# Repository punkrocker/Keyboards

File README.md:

# SweepPluck

34 键正交分体键盘，采用可翻面 PCB。两侧使用两片相同 PCB，在相反面装配。

本仓库仅包含 Pluck 版本。

- [工程、装配说明及验证结果](SweepPluck/README.txt)
- [主控焊接位置标记图](SweepPluck/mcu-guide/README.md)
- [电池与电源开关焊接图](SweepPluck/power-guide/README.md)
- [PCB 下单文件](SweepPluck/SweepPluck-JLCPCB.zip)
- [旅行便携盒](SweepPluck/travel-case/)
- [许可证](LICENSE)

设计基于 [Sweep](https://github.com/davidphilipbarr/Sweep)。Pluck 的历史设计归档保存在 `SweepPluck/archive/`。

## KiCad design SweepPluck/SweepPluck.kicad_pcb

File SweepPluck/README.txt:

SweepPluck v3.1 — 可翻面的正交分体键盘
======================================

电池与电源开关焊接图
  见 power-guide/README.md，含左手 F 面、右手 B 面焊盘图及焊接检查步骤。
  电池正极接 BATP1/BAT，负极接 BATG1/GND；开关 2–3 脚控制 BAT 到 RAW。

旅行便携盒
  travel-case/ 为裸 PCB + 3 mm 防滑垫配置的便携盒模型与 EVA 内托裁切图。
  轴体按 Choc V2，键帽高度按 K3 兼容矮键帽 4.4 mm 估算，主控为插座安装的 nice!nano。
  合拢外形约 108.05×92.80×44.80 mm；使用外部魔术贴绑带闭合。
  具体尺寸预算、安装限制和打印说明见 travel-case/使用说明.txt。
  tools/travel_case.py 可调整高度与主控安装间距预算；尚未实物试印。
  case/ 是之前的可选键盘底壳方案，使用上述旅行盒不需要制作该底壳。
  下方原有 ZIP 为此前生成的归档，不包含本次新增旅行盒，以目录中当前文件为准。

打开 SweepPluck.kicad_pro。
嘉立创 PCB 下单上传 SweepPluck-JLCPCB.zip。
它只包含 9 个生产层/钻孔文件，均位于 ZIP 根目录。
现在是一款 17 键单侧 PCB，同一份 Gerber 制作两片：
一片在 F 面安装键轴作为左手，另一片在 B 面安装键轴作为右手。
每片板都包含两种装配方式所需的孔和焊盘，不需要左右专用板。
原 v2 双侧拼板完整保存在 archive/SweepPluck-v2-panel.zip。

尺寸与布局
  整套 34 键，每侧 3×5 主键，加内侧第四排 2 个水平拇指键。
  键位与 v2 相同，全部为 0°，横纵键距均为 19.05 mm。
  单片 PCB 板框中心线尺寸：95.25×80.0 mm。
  板高由 77 mm 增至 80 mm，用于容纳主控的两组选装孔排。
  Gerber job 包围盒包含 0.05 mm 板框线宽，显示 95.30×80.05 mm。
  PCB 为 2 层 FR-4、1.6 mm 厚；USB/TRRS 插座可向板边外伸出。
  每片板有两个 3.2 mm 安装孔，仍位于原主键网格交点。
  此版本交付单片板；整套使用两片相同 PCB，没有折断桥。

主控焊接标记图
  见 mcu-guide/README.md，含左手 L 组、右手 R 组实际 PCB 标记及放大图。
  绿色圈出的两排共 24 孔为本侧主控焊孔，并标明 USB 朝向。

装配方法
  左手：将丝印 LEFT 的 F 面朝上，在此面装轴体、TRRS、电源及复位开关。
        主控装在 U1 的两排 L 孔中，USB 朝左侧外缘。
  右手：将丝印 RIGHT 的 B 面朝上，在此面装上述器件。
        主控装在同一 U1 封装的两排 R 孔中，USB 朝右侧外缘。

  主控区域共有四条横向孔排，按布局图方向从上到下依次为 L、R、L、R。
  左手选第 1 和第 3 排，右手选第 2 和第 4 排。
  两组选装孔排整体错开 2.54 mm，孔径为 1.0 mm。
  每组都是完整的 2×12 针 Pro Micro 接口，每块 PCB 只装一个主控。
  不需要 MCU 焊锡跳线，也不要短接另一组选装孔排。

  主控沿用 Sweep High M 的 FACE DOWN 安装方向：
  元件面、USB 插座所在面朝向键盘 PCB，而不是朝向键帽上方。
  用排针或插座留出元件和 USB 外壳的高度，不要将主控模块贴板焊接。
  两面均标有 FACE DOWN、L/R、TX 和 RAW，可用模块引脚标记核对方向。
  左手 L 组 USB 端的上排是 TX、下排是 RAW；
  右手 R 组从 B 面看 USB 端的上排是 RAW、下排是 TX。
  电源和复位开关均提供 F/B 两面焊盘，每个位置只在键轴所在面安装一个。
  轴体焊孔、TRRS 成对焊盘和电池通孔支持正反面装配。

轴体与电路
  保留原 Choc V1 / Choc V2 / MX / Alps 通用焊接兼容性，无热插拔。
  新轴体封装保留原钻孔中心并增加镜像孔位。
  MX/Alps 的两个无极性触点翻面后交换 GPIO/GND 接法；
  Choc 的中心触点仍接 GND，左右对称的另一触点接同一 GPIO。
  重叠的轴体圆孔/长孔已合并为连续镀铜长孔。
  中心定位孔为 4.9 mm，两侧定位孔仍为 2.17×1.8 mm NPTH 长孔。
  每侧 17 键直连，无矩阵二极管。
  两组选装孔的 24 针 GPIO、电源和复位映射均与 v2 左侧一致。
  每侧 68 个有效器件引脚连接与原设计核对一致。
  TRRS：R1=SERIAL（Pro Micro RX），R2=VCC，T/S=GND。
  电池正极 BAT 经电源开关接 RAW，负极接 GND，沿用原供电接法。
  引脚 CSV 包含网络、坐标、钻孔和 LEFT/RIGHT/BOTH 装配标记。
  预览数字 1–17 是 Switch1–Switch17 网络编号，不是实际键码。
  本次没有新增或烧录固件；左右手选择由对应 QMK/ZMK 固件配置。

定位板
  SweepPluck-plate.kicad_pcb / .dxf 是可翻面的单侧定位板，DXF 单位为毫米。
  两侧各用一片相同定位板，右手翻面使用。
  下方外侧开口避让两组选装主控及其他器件。
  默认 14×14 mm 轴孔供适配该尺寸的 MX/Choc 使用。
  Alps 定位板开口不同，使用 Alps 时需按实际轴体另改定位板。
  网格交点上的固定件需低于键帽活动空间，可使用平头/沉头方案。

交付文件
  SweepPluck-v3-reversible.zip：完整 v3 工程包，包含本地库、脚本、检查报告和来源归档。
  SweepPluck.kicad_pro / .kicad_pcb / .kicad_sch：v3 主工程。
  SweepPluck.kicad_sym、SweepPluck.pretty、库表：本地符号与可翻面封装。
  SweepPluck-preview.png / SweepPluck-layout.svg：左右手装配示意。
  SweepPluck-preview.svg / SweepPluck-preview-pcb.png：实际 F 面 PCB。
  SweepPluck-back.svg / SweepPluck-back-pcb.png：镜像显示的实际 B 面 PCB。
  SweepPluck-plate.kicad_pcb / .dxf / .svg：单侧定位板。
  SweepPluck-pins.csv：引脚、网络和孔排核对表。
  SweepPluck-JLCPCB.zip / SweepPluck-gerbers.zip：相同的专用下单包，共 9 文件。
    包含两面铜层、阻焊、丝印、GKO 板框和独立 PTH/NPTH 钻孔。
    使用标准 RS-274X、Protel 扩展名、毫米十进制 Excellon，绘图坐标为非负值。
    不含工程、嵌套压缩包、Gerber job 或 X2/网络扩展属性。
  gerbers/：KiCad 原始导出文件，另外保留一个 Gerber job，目录共 10 文件。
  verification/summary.json：最终检查结果与板文件、生产文件 SHA-256。
  verification/fabrication-check.json：对实际下单 ZIP 的独立 Gerbv 解析及开窗/钻孔核对报告。
  archive/SweepPluck-v2-panel.zip：改动前双侧拼板及全部配套文件。
  archive/SweepPluck-v1-split.zip：更早的左右独立工程。

验证与限制
  KiCad 10.0.7：PCB DRC 0 违规、0 未连接、0 原理图一致性问题。
  原理图 ERC 0 违规，定位板 DRC 0 违规。
  102 项触点检查覆盖每个键的 MX、Alps、Choc 两面安装接法。
  原 153 个轴体钻孔中心全部保留，原键位与 GPIO 映射核对通过。
  主控外形与键帽、定位板避让区核对通过。
  v3.1 修复了布线导入后通孔焊盘阻焊开窗丢失的问题。
  211 个通孔焊盘均有双面开窗；每面导出的 277 个开窗逐项核对通过。
  专用包 9 文件经 Gerbv 2.10.0 独立解析：0 错误、0 警告。
  镀铜钻孔/槽 222 个（包含过孔），非镀铜孔/槽 57 个，与 PCB 数量一致。
  尚未在嘉立创账户中完成在线上传实测。
  线宽 >=0.20 mm、电气间距 >=0.20 mm、铜到板边/钻孔 >=0.25 mm。
  走线为 0.25 mm，过孔为 0.60/0.30 mm。
  原理图为被动引脚连接图，ERC 不检查 MCU 引脚方向或模块供电/充电能力。
  尚未实物打样；插座高度、实际模块外形及轴体/定位板装配仍需打样确认。

重新生成（当前文件已生成，无需运行）
  使用能 import pcbnew 的 KiCad Python，并确保 kicad-cli 位于 PATH。
  cairosvg 用于 PNG 预览，布线需 Java 21 和 Freerouting 2.1.0。
  从仓库根目录运行：
    python SweepPluck/tools/reversible.py build
    python SweepPluck/tools/reversible.py route --jar /path/to/freerouting-2.1.0.jar
    python SweepPluck/tools/reversible.py import
    python SweepPluck/tools/reversible.py checks
  build 从 v2 归档重建 v3，会覆盖 PCB 为未布线版。
  若 checks 仅有 track_dangling 警告且无未连接项，运行：
    python SweepPluck/tools/reversible.py clean
  clean 只移除 DRC 明确报告的冗余支线，不忽略检查项。
  完成后：
    python SweepPluck/tools/reversible.py placement
    python SweepPluck/tools/reversible.py export
    python SweepPluck/tools/check_fabrication.py
  export 会先核对检查报告与当前 PCB、原理图、定位板及规则，再导出生产文件。
  check_fabrication 需安装 gerbv，检查专用下单包的实际文件与 PCB 数据。
  手动编辑 PCB 后可用 refresh 更新辅助文件，再执行 checks 和 export。
  compact.py 转发到同一 v3 生成器；preview.py 生成 v3 装配图。
  如需重新打包完整工程，运行 python SweepPluck/tools/package.py。

参考与授权
  原接口/键位来源为本仓库 Sweep High；可翻面结构参考 Sweep High M / Sweep Half Swept。
  主控安装方向参考 gallery/sweep-high-m/front.png 的 Face down 标记。
  nice!nano 引脚图：https://nicekeyboards.com/docs/nice-nano/pinout-schematic/
  Freerouting：https://github.com/freerouting/freerouting/releases/tag/v2.1.0
  授权沿用本仓库 LICENSE。

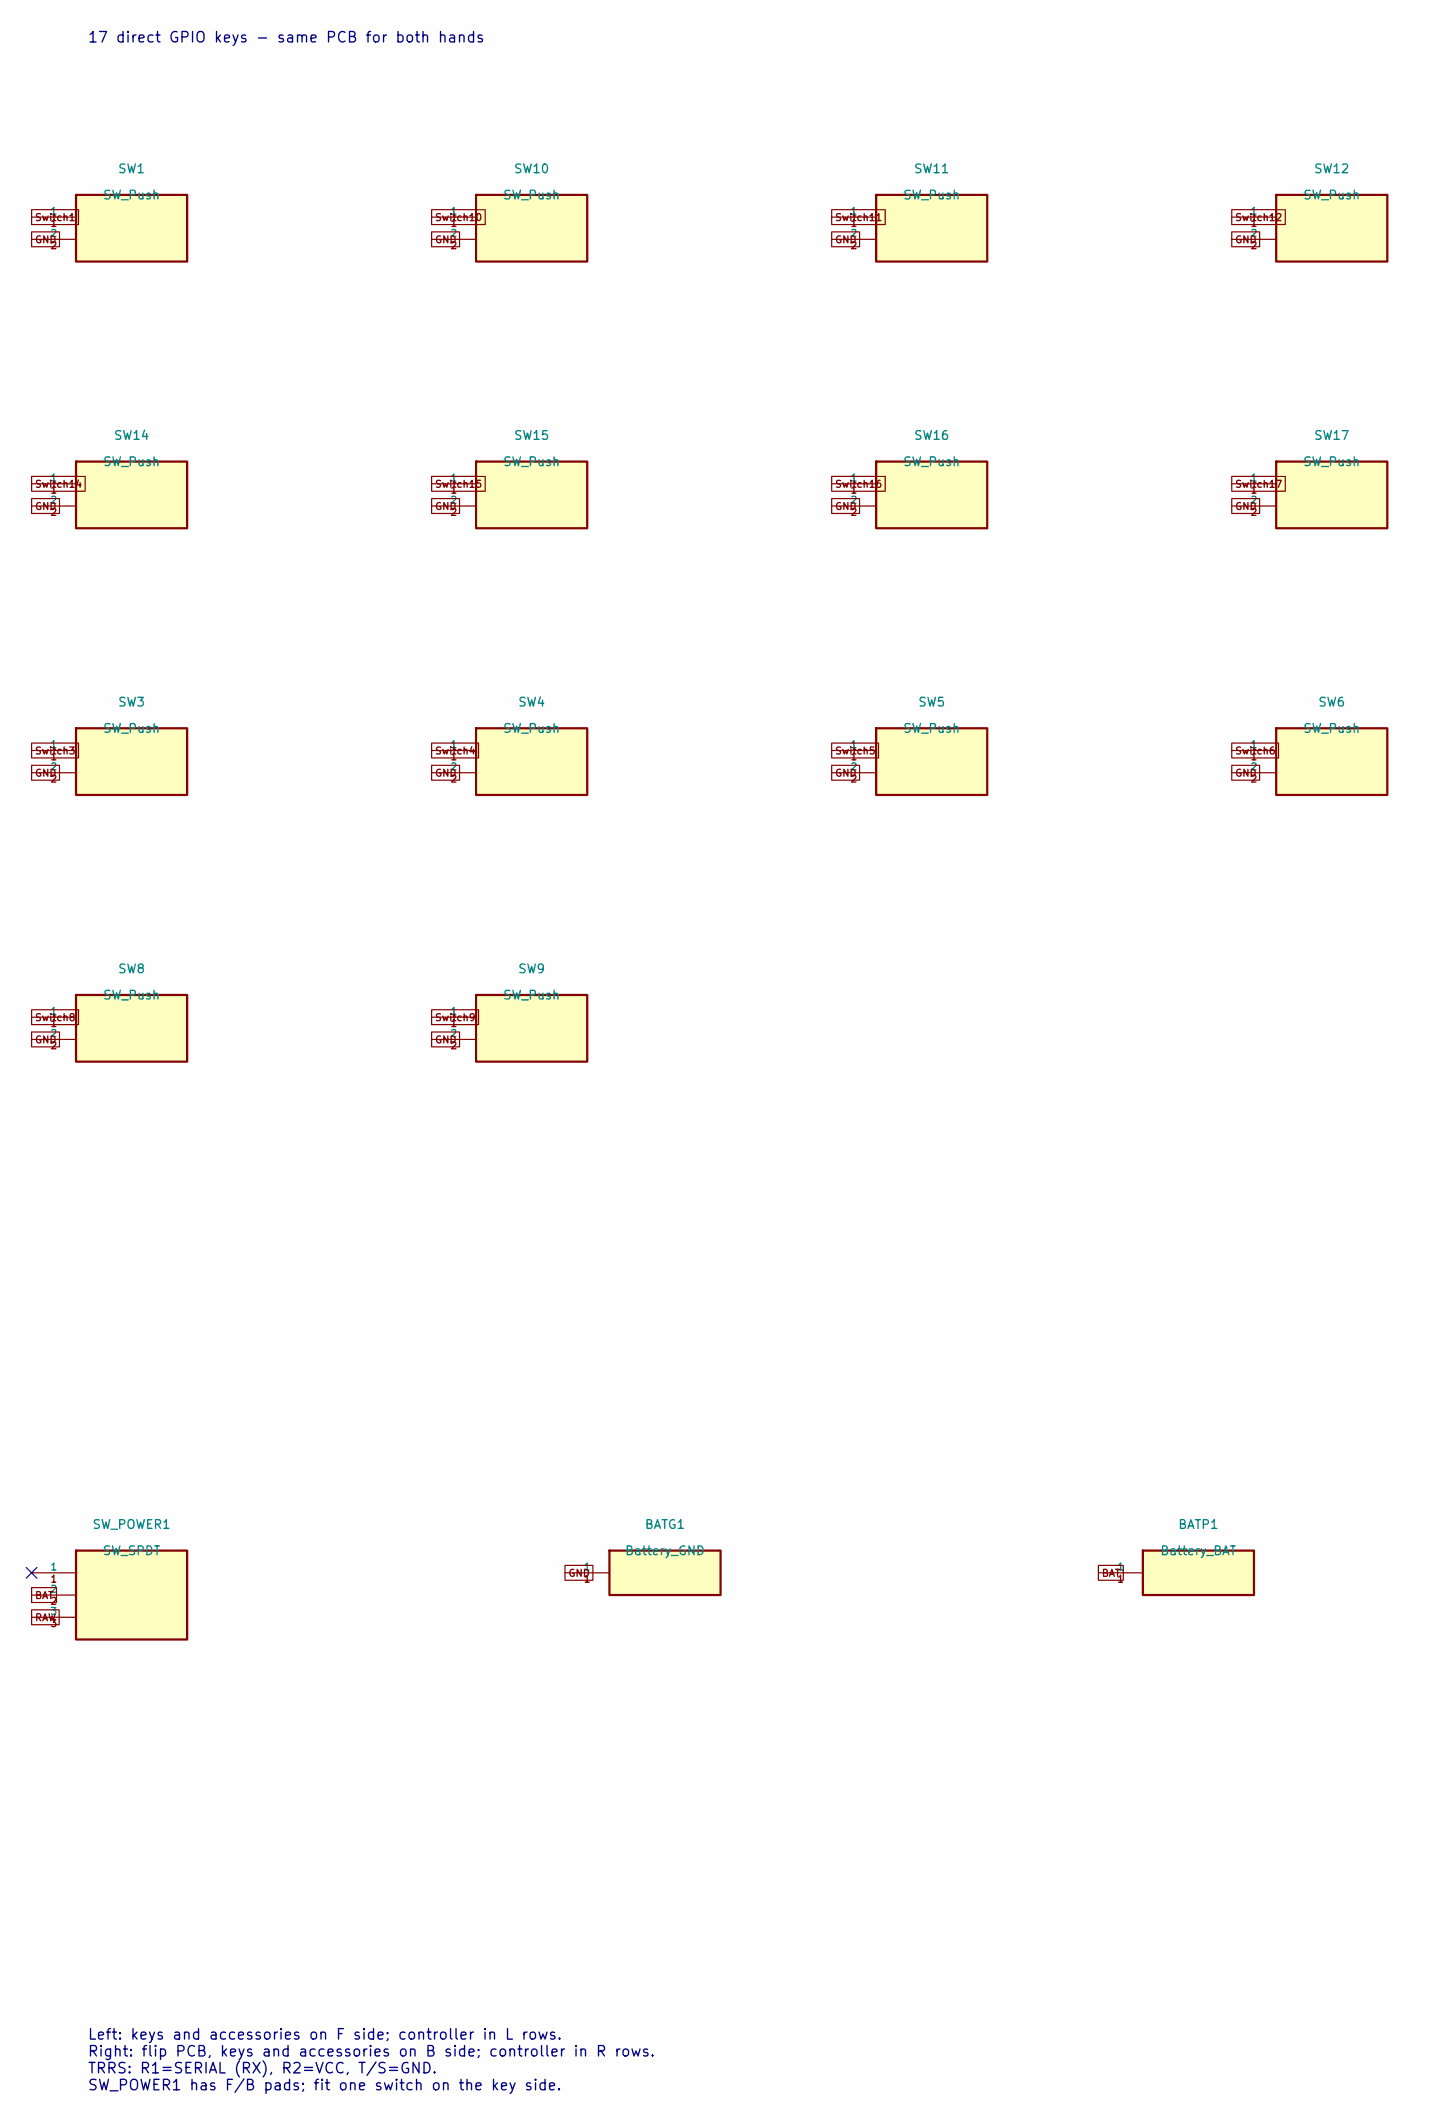
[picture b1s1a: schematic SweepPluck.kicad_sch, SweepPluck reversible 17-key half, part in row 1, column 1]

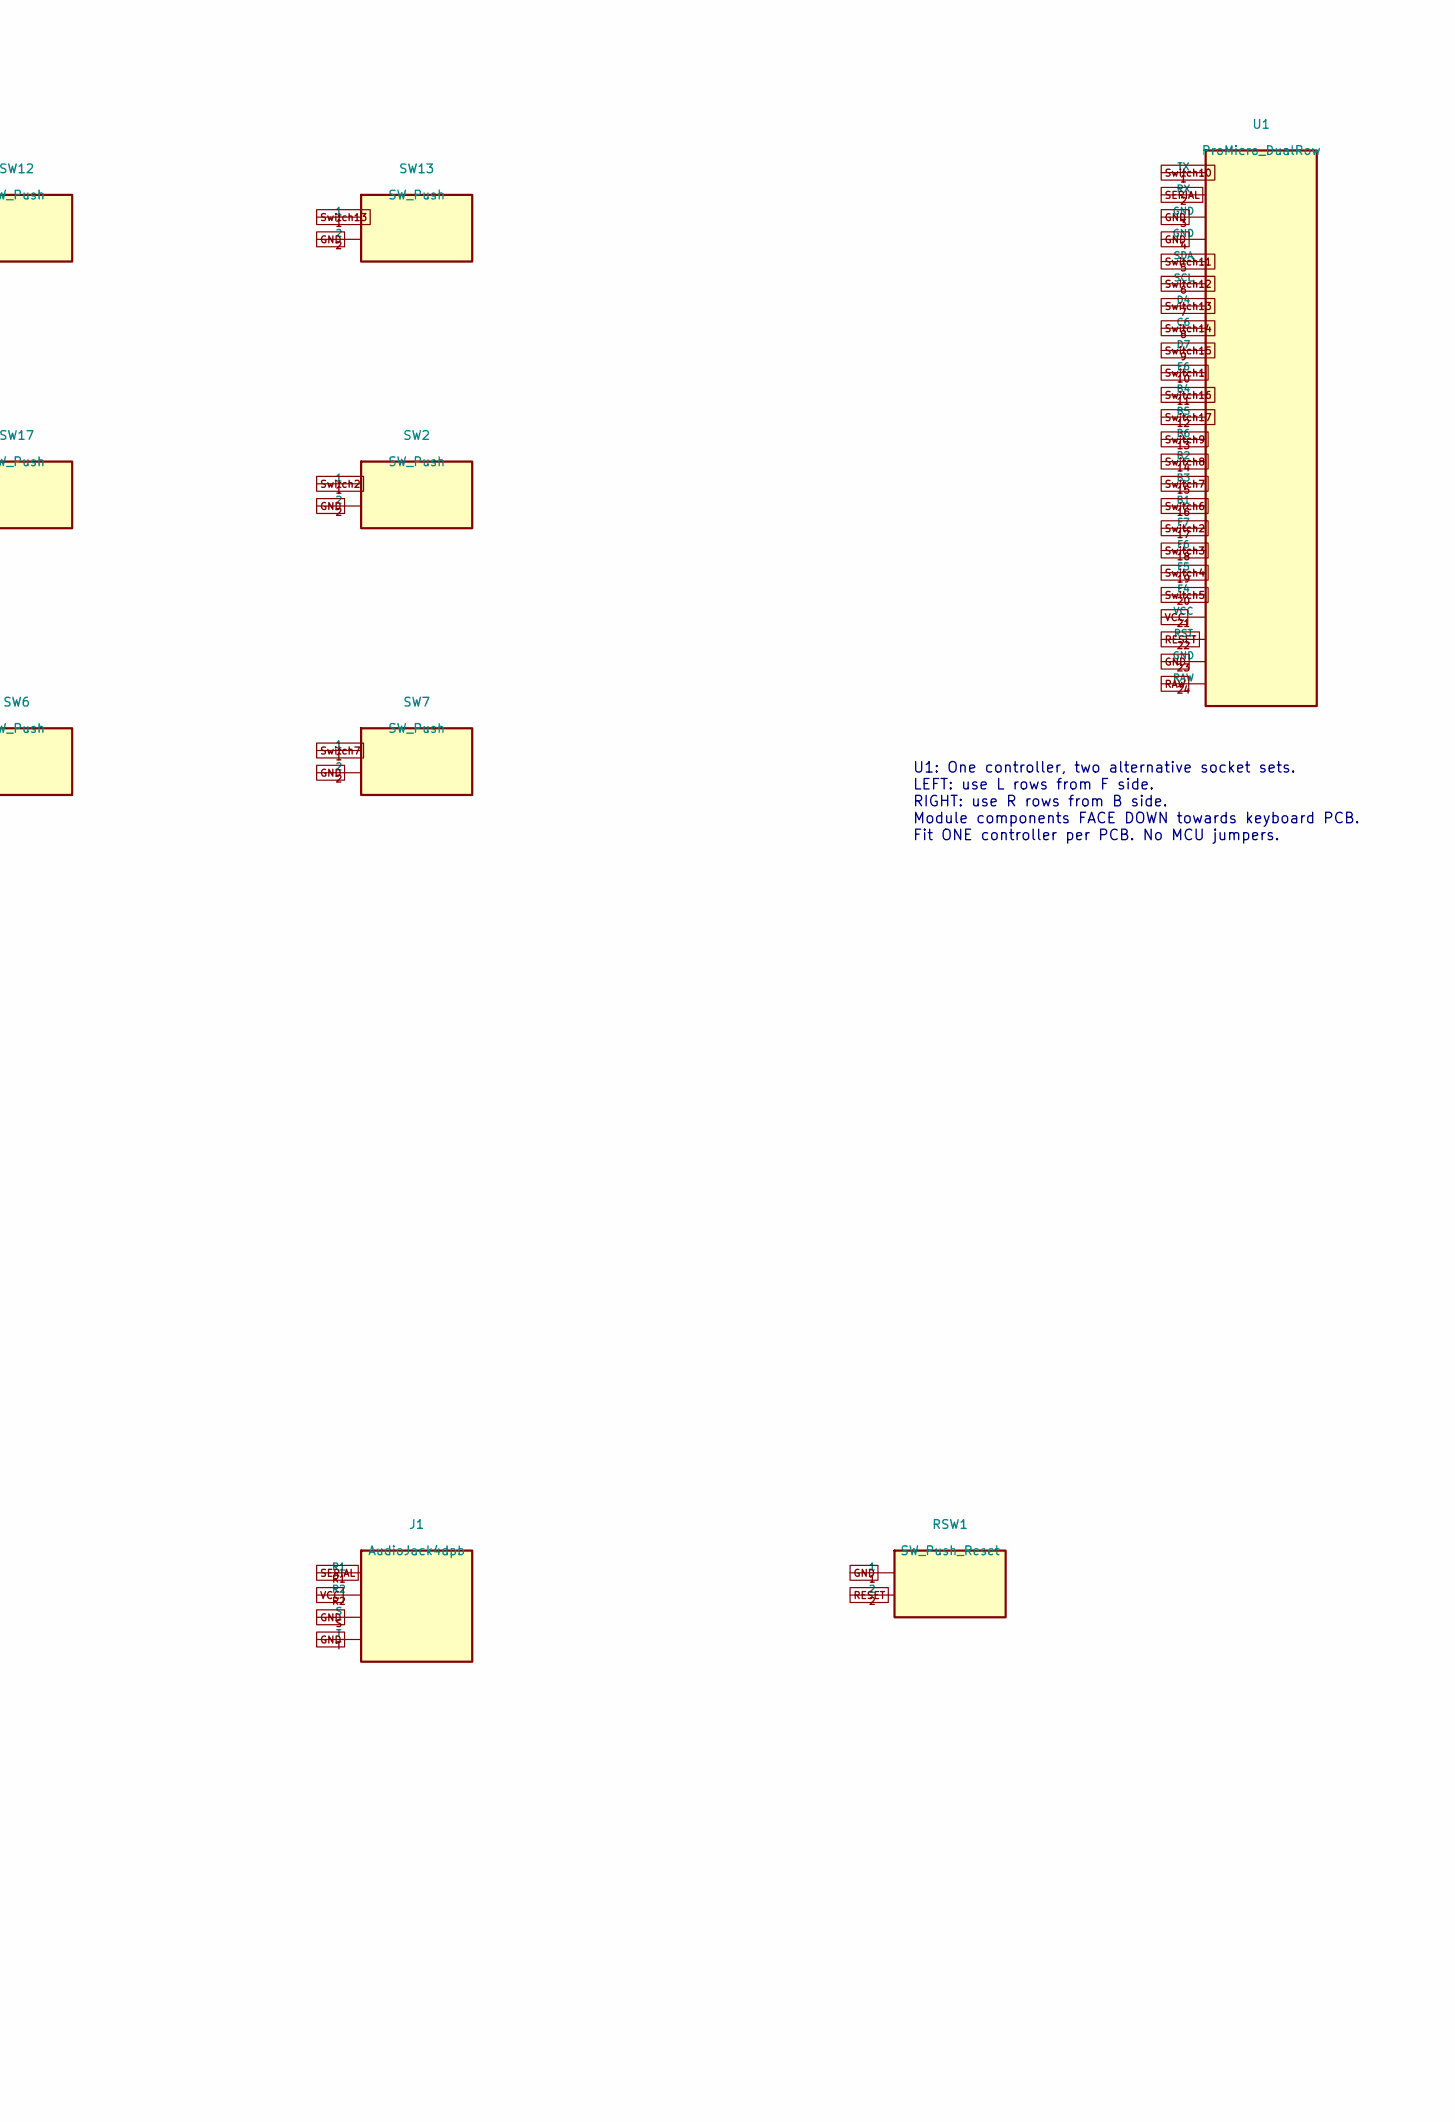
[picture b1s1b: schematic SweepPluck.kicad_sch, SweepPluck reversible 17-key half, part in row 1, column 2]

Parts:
BATG1: Battery_GND; Battery_Pad
BATP1: Battery_BAT; Battery_Pad
J1: AudioJack4dpb; TRRS_Reversible
RSW1: SW_Push_Reset; Reset_Reversible
SW1, SW2, SW3, SW4, SW5, SW6, SW7, SW8, SW9, SW10, SW11, SW12, SW13, SW14, SW15, SW16, SW17: SW_Push; Universal_Reversible
SW_POWER1: SW_SPDT; Power_Reversible
U1: ProMicro_DualRow

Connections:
BAT: BATP1.1, SW_POWER1.2
GND: BATG1.1, J1.S, J1.T, RSW1.1, SW1.2, SW2.2, SW3.2, SW4.2, SW5.2, SW6.2, SW7.2, SW8.2, SW9.2, SW10.2, SW11.2, SW12.2, SW13.2, SW14.2, SW15.2, SW16.2, SW17.2, U1.3 (GND), U1.4 (GND), U1.23 (GND)
RAW: SW_POWER1.3, U1.24 (RAW)
RESET: RSW1.2, U1.22 (RST)
SERIAL: J1.R1, U1.2 (RX)
Switch1: SW1.1, U1.10 (E6)
Switch2: SW2.1, U1.17 (F7)
Switch3: SW3.1, U1.18 (F6)
Switch4: SW4.1, U1.19 (F5)
Switch5: SW5.1, U1.20 (F4)
Switch6: SW6.1, U1.16 (B1)
Switch7: SW7.1, U1.15 (B3)
Switch8: SW8.1, U1.14 (B2)
Switch9: SW9.1, U1.13 (B6)
Switch10: SW10.1, U1.1 (TX)
Switch11: SW11.1, U1.5 (SDA)
Switch12: SW12.1, U1.6 (SCL)
Switch13: SW13.1, U1.7 (D4)
Switch14: SW14.1, U1.8 (C6)
Switch15: SW15.1, U1.9 (D7)
Switch16: SW16.1, U1.11 (B4)
Switch17: SW17.1, U1.12 (B5)
VCC: J1.R2, U1.21 (VCC)

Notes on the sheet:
17 direct GPIO keys - same PCB for both hands
U1: One controller, two alternative socket sets. LEFT: use L rows from F side. RIGHT: use R rows from B side. Module components FACE DOWN towards keyboard PCB. Fit ONE controller per PCB. No MCU jumpers.
Left: keys and accessories on F side; controller in L rows. Right: flip PCB, keys and accessories on B side; controller in R rows. TRRS: R1=SERIAL (RX), R2=VCC, T/S=GND. SW_POWER1 has F/B pads; fit one switch on the key side.

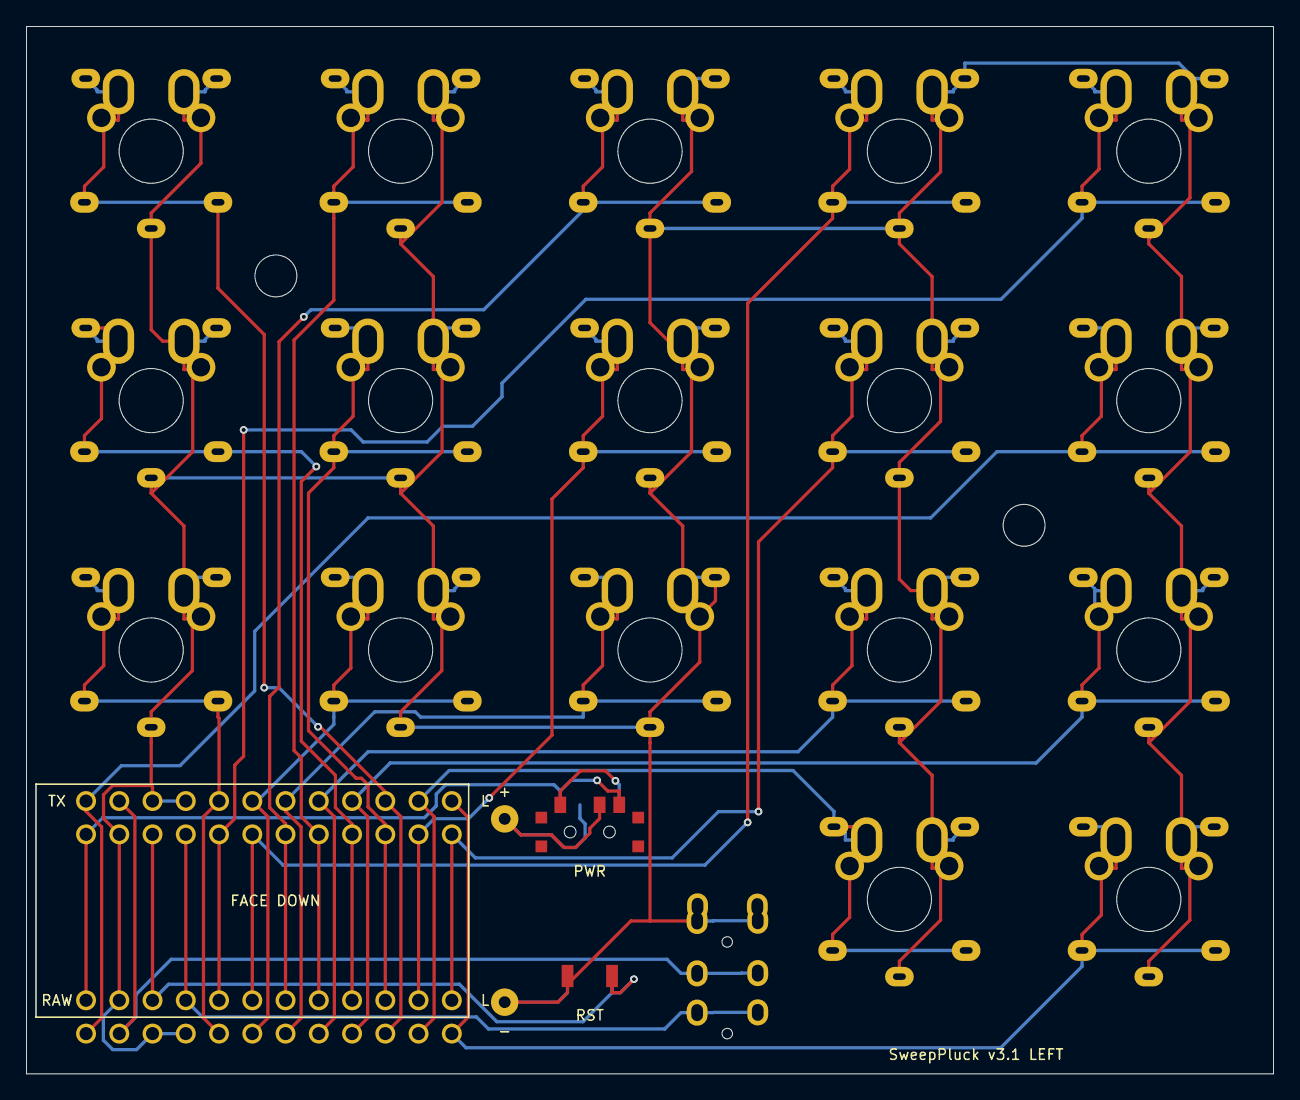
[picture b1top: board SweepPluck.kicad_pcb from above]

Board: 2 copper layers, 95.2 x 80.0 mm, 25 parts (0 on the bottom side), 23 nets.

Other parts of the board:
H1, H2: MountingHole_3.2mm

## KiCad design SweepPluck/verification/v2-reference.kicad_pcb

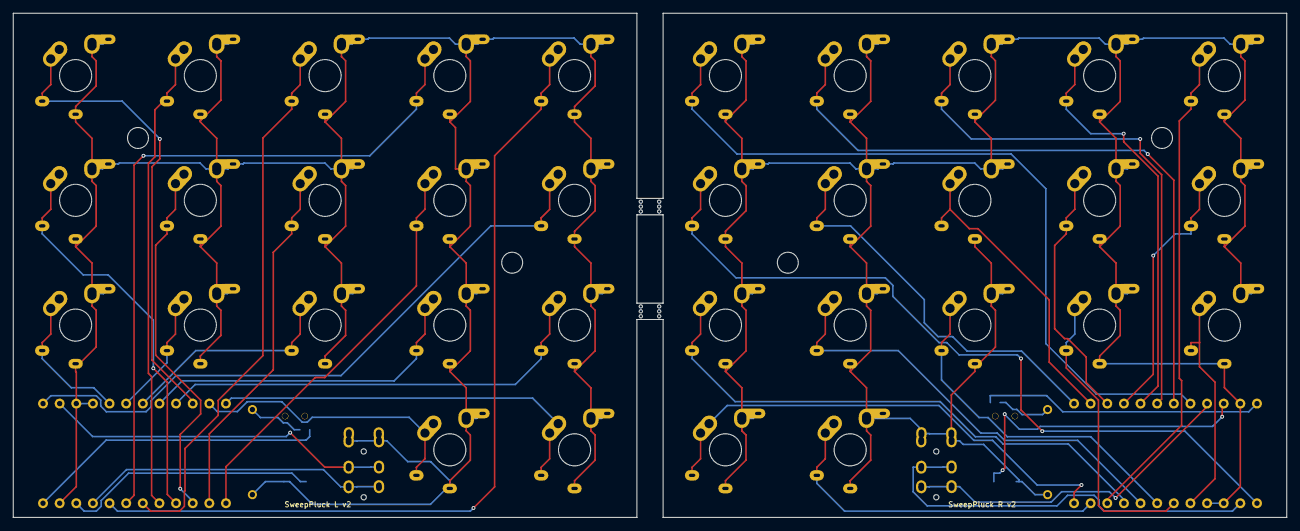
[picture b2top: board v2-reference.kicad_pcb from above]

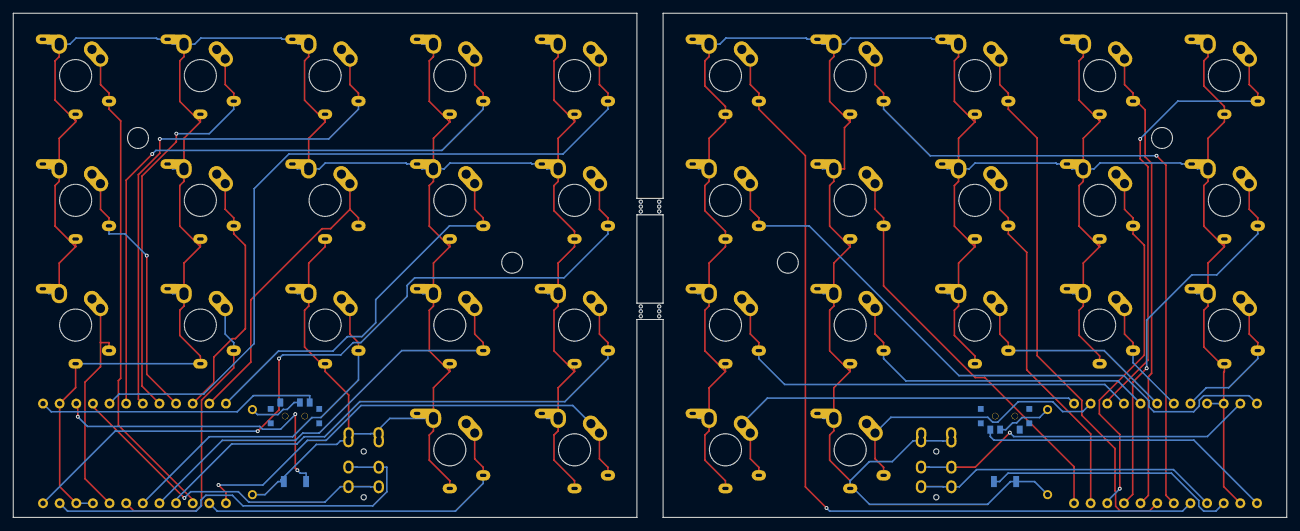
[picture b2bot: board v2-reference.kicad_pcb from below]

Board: 2 copper layers, 194.5 x 77.0 mm, 54 parts (4 on the bottom side), 46 nets.

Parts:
BATG1, BATG2: MountingHole_Pad; 1pin_conn
BATP1, BATP2: MountingHole_Pad; 1pin_conn
H1, H2, H3, H4: MountingHole_3.2mm
J1, J2: AudioJack4dpb; TRRS-PJ-DPB2
MB1, MB2, MB3, MB4: Mousebite_3x0.5_P0.75
RSW1, RSW2: SW_Push; SW_SPST_B3U-1000P
SW2, SW2_r1, SW3, SW3_r1, SW4, SW4_r1, SW5, SW5_r1, SW6, SW6_r1, SW7_r1, SW8, SW8_r1, SW9, SW9_r1, SW10, SW11, SW11_r1, SW12, SW12_r1, SW13_r1, SW14, SW15, SW15_r1, SW16, SW16_r1, SW17, SW17_r1, SW18, SW18_r1, SW20, SW20_r1, SW21, SW21_r1: SW_Push; keyswitch_cherrymx_alps_choc12_slots_1u
SW_POWER1: SW_SPDT; SPDT_C128955
SW_POWERR1: SW_SPDT; SPDT_C128955
U1, U2: ProMicro-kbd; ProMicro_v3_min

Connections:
BAT_L: BATP1.1, SW_POWER1.2
BAT_R: BATP2.1, SW_POWERR1.2
GND_L: BATG1.1, J1.S, J1.T, RSW1.1, SW2.2, SW3.2, SW4.2, SW5.2, SW6.2, SW8.2, SW9.2, SW10.2, SW11.2, SW12.2, SW14.2, SW15.2, SW16.2, SW17.2, SW18.2, SW20.2, SW21.2, U1.3, U1.4, U1.23
GND_R: BATG2.1, J2.S, J2.T, RSW2.1, SW2_r1.2, SW3_r1.2, SW4_r1.2, SW5_r1.2, SW6_r1.2, SW7_r1.2, SW8_r1.2, SW9_r1.2, SW11_r1.2, SW12_r1.2, SW13_r1.2, SW15_r1.2, SW16_r1.2, SW17_r1.2, SW18_r1.2, SW20_r1.2, SW21_r1.2, U2.3, U2.4, U2.23
RAW_L: SW_POWER1.3, U1.24
RAW_R: SW_POWERR1.3, U2.24
RESET_L: RSW1.2, U1.22
RESET_R: RSW2.2, U2.22
SERIAL_L: J1.R1, U1.2
SERIAL_R: J2.R1, U2.2
Switch1: SW2.1, U1.10
Switch1_r: SW2_r1.1, U2.10
Switch2: SW3.1, U1.17
Switch2_r: SW3_r1.1, U2.17
Switch3: SW4.1, U1.18
Switch3_r: SW4_r1.1, U2.18
Switch4: SW5.1, U1.19
Switch4_r: SW5_r1.1, U2.19
Switch5: SW6.1, U1.20
Switch5_r: SW6_r1.1, U2.20
Switch6: SW8.1, U1.16
Switch6_r: SW7_r1.1, U2.16
Switch7: SW9.1, U1.15
Switch7_r: SW8_r1.1, U2.15
Switch8: SW10.1, U1.14
Switch8_r: SW9_r1.1, U2.14
Switch9: SW11.1, U1.13
Switch9_r: SW11_r1.1, U2.13
Switch10: SW12.1, U1.1
Switch10_r: SW12_r1.1, U2.1
Switch11: SW14.1, U1.5
Switch11_r: SW13_r1.1, U2.5
Switch12: SW15.1, U1.6
Switch12_r: SW18_r1.1, U2.6
Switch13: SW16.1, U1.7
Switch13_r: SW15_r1.1, U2.7
Switch14: SW17.1, U1.8
Switch14_r: SW16_r1.1, U2.8
Switch15: SW18.1, U1.9
Switch15_r: SW17_r1.1, U2.9
Switch16: SW21.1, U1.11
Switch16_r: SW21_r1.1, U2.11
Switch17: SW20.1, U1.12
Switch17_r: SW20_r1.1, U2.12
VCC_L: J1.R2, U1.21
VCC_R: J2.R2, U2.21
